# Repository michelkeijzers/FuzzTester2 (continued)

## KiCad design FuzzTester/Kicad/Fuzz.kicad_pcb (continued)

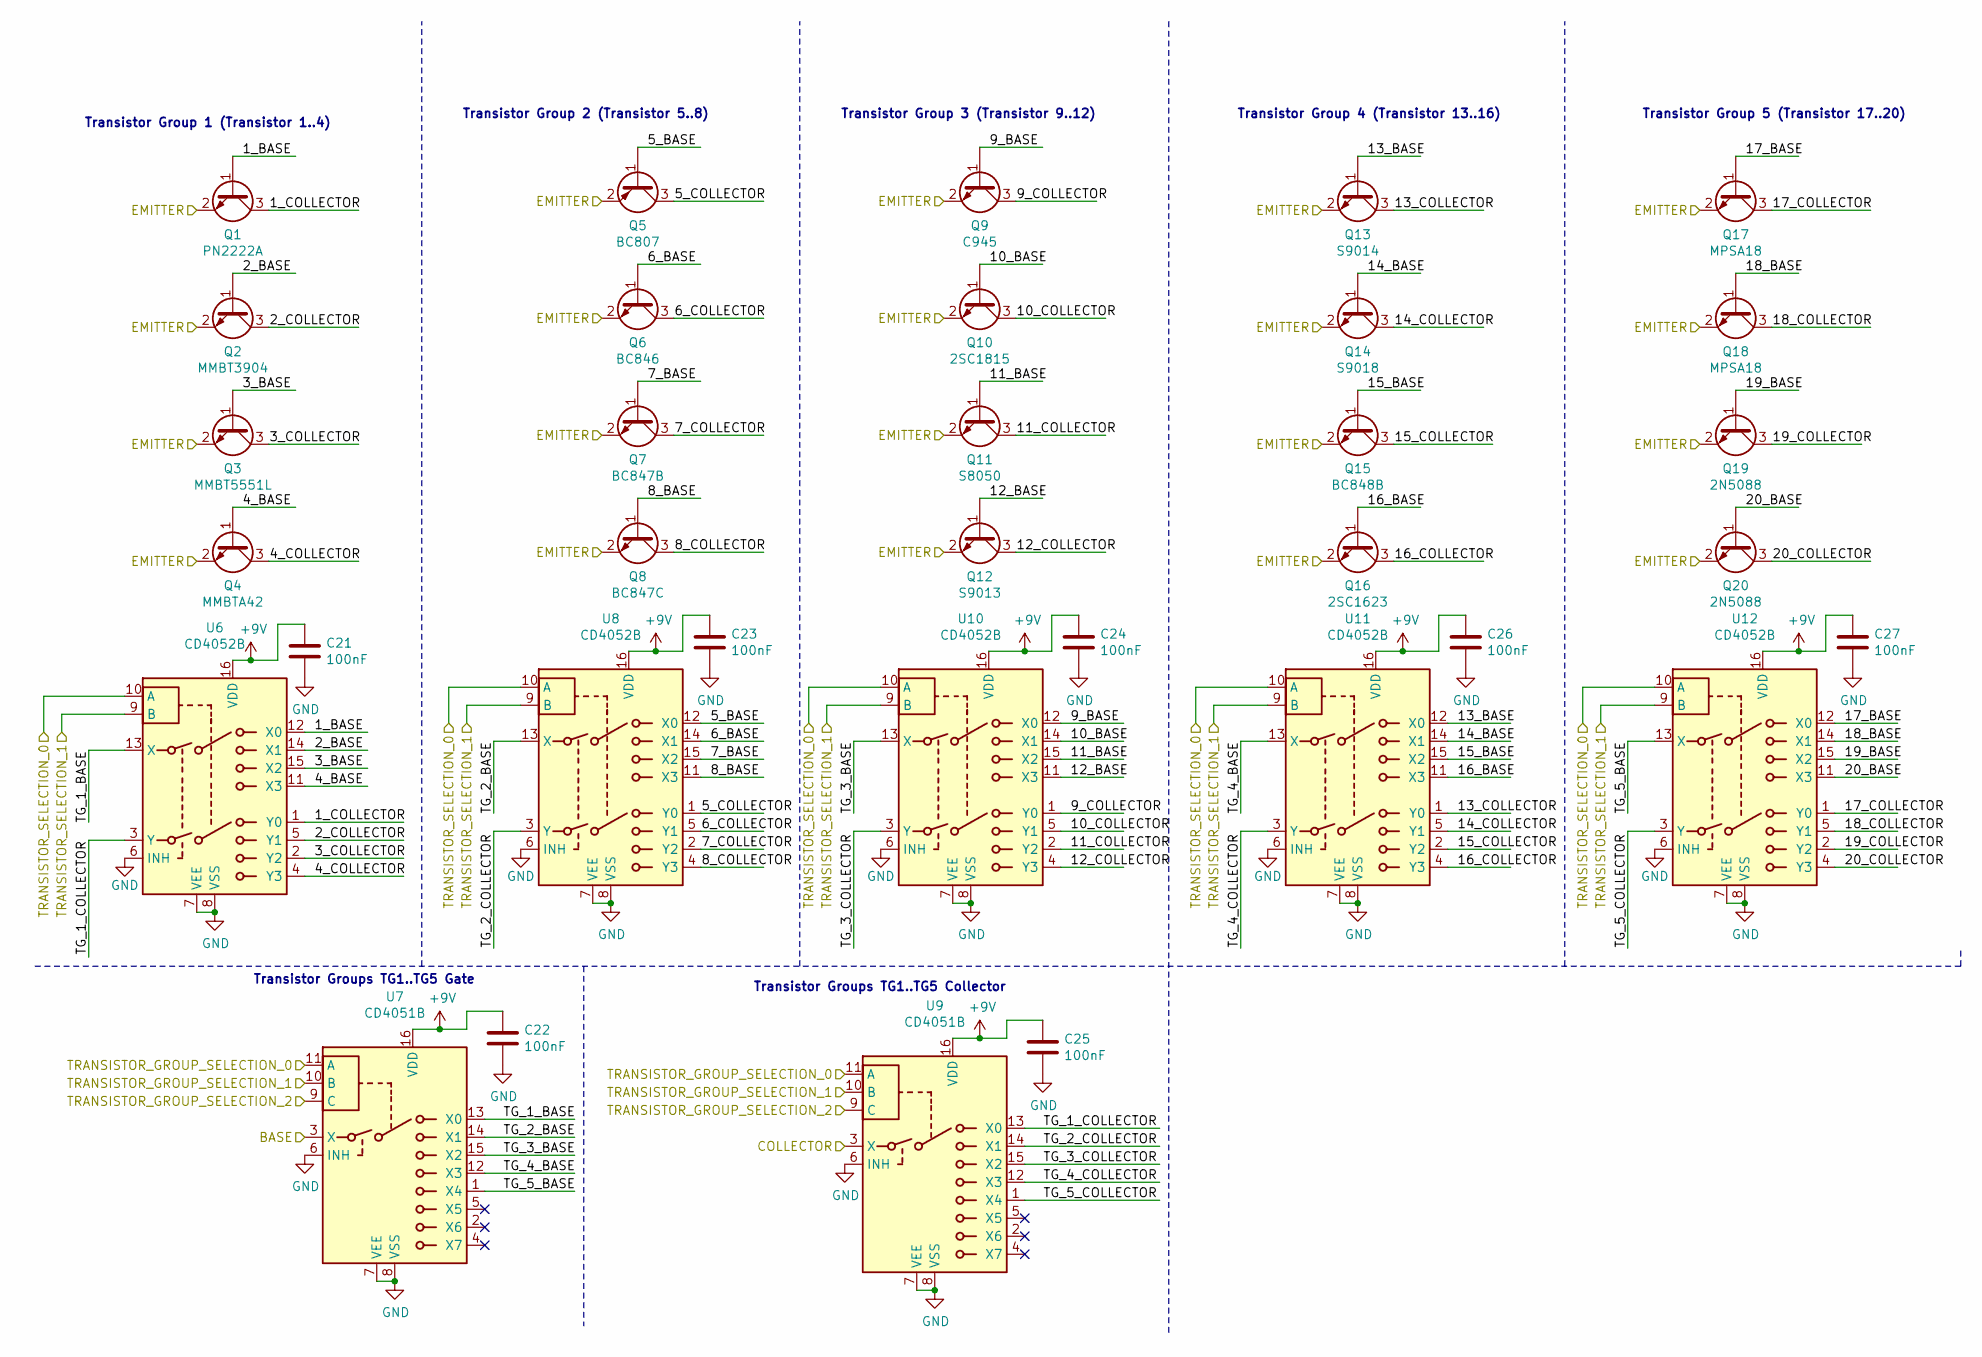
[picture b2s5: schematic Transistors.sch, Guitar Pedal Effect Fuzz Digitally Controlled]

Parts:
C21, C22, C23, C24, C25, C26, C27: 100nF; C_0805_2012Metric_Pad1.15x1.40mm_HandSolder
Q1: PN2222A; SOT-23_Handsoldering
Q2: MMBT3904; SOT-23_Handsoldering
Q3: MMBT5551L; SOT-23_Handsoldering
Q4: MMBTA42; SOT-23_Handsoldering
Q5: BC807; SOT-23_Handsoldering
Q6: BC846; SOT-23_Handsoldering
Q7: BC847B; SOT-23_Handsoldering
Q8: BC847C; SOT-23_Handsoldering
Q9: C945; SOT-23_Handsoldering
Q10: 2SC1815; SOT-23_Handsoldering
Q11: S8050; SOT-23_Handsoldering
Q12: S9013; SOT-23_Handsoldering
Q13: S9014; SOT-23_Handsoldering
Q14: S9018; SOT-23_Handsoldering
Q15: BC848B; SOT-23_Handsoldering
Q16: 2SC1623; SOT-23_Handsoldering
Q17, Q18: MPSA18; TO-92_Inline
Q19, Q20: 2N5088; TO-92_Inline
U6, U8, U10, U11, U12: CD4052B; SOIC-16_3.9x9.9mm_P1.27mm
U7, U9: CD4051B; SOIC-16_3.9x9.9mm_P1.27mm

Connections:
+9V: C21.1, C22.1, C23.1, C24.1, C25.1, C26.1, C27.1, U6.16 (VDD), U7.16 (VDD), U8.16 (VDD), U9.16 (VDD), U10.16 (VDD), U11.16 (VDD), U12.16 (VDD); also elsewhere on the board
/TRANSISTOR_B_GROUP_SELECTION_0: U7.11 (A), U9.11 (A); also elsewhere on the board
/TRANSISTOR_B_GROUP_SELECTION_1: U7.10 (B), U9.10 (B); also elsewhere on the board
/TRANSISTOR_B_GROUP_SELECTION_2: U7.9 (C), U9.9 (C); also elsewhere on the board
/TRANSISTOR_B_SELECTION_0: U6.10 (A), U8.10 (A), U10.10 (A), U11.10 (A), U12.10 (A); also elsewhere on the board
/TRANSISTOR_B_SELECTION_1: U6.9 (B), U8.9 (B), U10.9 (B), U11.9 (B), U12.9 (B); also elsewhere on the board
/TransistorsB/1_BASE: Q1.1 (B), U6.12 (X0)
/TransistorsB/1_COLLECTOR: Q1.3 (C), U6.1 (Y0)
/TransistorsB/2_BASE: Q2.1 (B), U6.14 (X1)
/TransistorsB/2_COLLECTOR: Q2.3 (C), U6.5 (Y1)
/TransistorsB/3_BASE: Q3.1 (B), U6.15 (X2)
/TransistorsB/3_COLLECTOR: Q3.3 (C), U6.2 (Y2)
/TransistorsB/4_BASE: Q4.1 (B), U6.11 (X3)
/TransistorsB/4_COLLECTOR: Q4.3 (C), U6.4 (Y3)
/TransistorsB/5_BASE: Q5.1 (B), U8.12 (X0)
/TransistorsB/5_COLLECTOR: Q5.3 (C), U8.1 (Y0)
/TransistorsB/6_BASE: Q6.1 (B), U8.14 (X1)
/TransistorsB/6_COLLECTOR: Q6.3 (C), U8.5 (Y1)
/TransistorsB/7_BASE: Q7.1 (B), U8.15 (X2)
/TransistorsB/7_COLLECTOR: Q7.3 (C), U8.2 (Y2)
/TransistorsB/8_BASE: Q8.1 (B), U8.11 (X3)
/TransistorsB/8_COLLECTOR: Q8.3 (C), U8.4 (Y3)
/TransistorsB/9_BASE: Q9.1 (B), U10.12 (X0)
/TransistorsB/9_COLLECTOR: Q9.3 (C), U10.1 (Y0)
/TransistorsB/10_BASE: Q10.1 (B), U10.14 (X1)
/TransistorsB/10_COLLECTOR: Q10.3 (C), U10.5 (Y1)
/TransistorsB/11_BASE: Q11.1 (B), U10.15 (X2)
/TransistorsB/11_COLLECTOR: Q11.3 (C), U10.2 (Y2)
/TransistorsB/12_BASE: Q12.1 (B), U10.11 (X3)
/TransistorsB/12_COLLECTOR: Q12.3 (C), U10.4 (Y3)
/TransistorsB/13_BASE: Q13.1 (B), U11.12 (X0)
/TransistorsB/13_COLLECTOR: Q13.3 (C), U11.1 (Y0)
/TransistorsB/14_BASE: Q14.1 (B), U11.14 (X1)
/TransistorsB/14_COLLECTOR: Q14.3 (C), U11.5 (Y1)
/TransistorsB/15_BASE: Q15.1 (B), U11.15 (X2)
/TransistorsB/15_COLLECTOR: Q15.3 (C), U11.2 (Y2)
/TransistorsB/16_BASE: Q16.1 (B), U11.11 (X3)
/TransistorsB/16_COLLECTOR: Q16.3 (C), U11.4 (Y3)
/TransistorsB/17_BASE: Q17.1 (B), U12.12 (X0)
/TransistorsB/17_COLLECTOR: Q17.3 (C), U12.1 (Y0)
/TransistorsB/18_BASE: Q18.1 (B), U12.14 (X1)
/TransistorsB/18_COLLECTOR: Q18.3 (C), U12.5 (Y1)
/TransistorsB/19_BASE: Q19.1 (B), U12.15 (X2)
/TransistorsB/19_COLLECTOR: Q19.3 (C), U12.2 (Y2)
/TransistorsB/20_BASE: Q20.1 (B), U12.11 (X3)
/TransistorsB/20_COLLECTOR: Q20.3 (C), U12.4 (Y3)
/TransistorsB/BASE: U7.3 (X); also elsewhere on the board
/TransistorsB/TG_1_BASE: U6.13 (X), U7.13 (X0)
/TransistorsB/TG_1_COLLECTOR: U6.3 (Y), U9.13 (X0)
/TransistorsB/TG_2_BASE: U7.14 (X1), U8.13 (X)
/TransistorsB/TG_2_COLLECTOR: U8.3 (Y), U9.14 (X1)
/TransistorsB/TG_3_BASE: U7.15 (X2), U10.13 (X)
/TransistorsB/TG_3_COLLECTOR: U9.15 (X2), U10.3 (Y)
/TransistorsB/TG_4_BASE: U7.12 (X3), U11.13 (X)
/TransistorsB/TG_4_COLLECTOR: U9.12 (X3), U11.3 (Y)
/TransistorsB/TG_5_BASE: U7.1 (X4), U12.13 (X)
/TransistorsB/TG_5_COLLECTOR: U9.1 (X4), U12.3 (Y)
/TransistorsC/BASE: U9.3 (X); also elsewhere on the board
GND: C21.2, C22.2, C23.2, C24.2, C25.2, C26.2, C27.2, U6.6 (INH), U6.7 (VEE), U6.8 (VSS), U7.6 (INH), U7.7 (VEE), U7.8 (VSS), U8.6 (INH), U8.7 (VEE), U8.8 (VSS), U9.6 (INH), U9.7 (VEE), U9.8 (VSS), U10.6 (INH), U10.7 (VEE), U10.8 (VSS), U11.6 (INH), U11.7 (VEE), U11.8 (VSS), U12.6 (INH), U12.7 (VEE), U12.8 (VSS); also elsewhere on the board
GNDA: Q1.2 (E), Q2.2 (E), Q3.2 (E), Q4.2 (E), Q5.2 (E), Q6.2 (E), Q7.2 (E), Q8.2 (E), Q9.2 (E), Q10.2 (E), Q11.2 (E), Q12.2 (E), Q13.2 (E), Q14.2 (E), Q15.2 (E), Q16.2 (E), Q17.2 (E), Q18.2 (E), Q19.2 (E), Q20.2 (E); also elsewhere on the board

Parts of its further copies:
C28, C29, C30, C31, C32, C33, C34: 100nF; C_0805_2012Metric_Pad1.15x1.40mm_HandSolder
Q21: PN2222A; SOT-23_Handsoldering
Q22: MMBT3904; SOT-23_Handsoldering
Q23: MMBT5551L; SOT-23_Handsoldering
Q24: MMBTA42; SOT-23_Handsoldering
Q25: BC807; SOT-23_Handsoldering
Q26: BC846; SOT-23_Handsoldering
Q27: BC847B; SOT-23_Handsoldering
Q28: BC847C; SOT-23_Handsoldering
Q29: C945; SOT-23_Handsoldering
Q30: 2SC1815; SOT-23_Handsoldering
Q31: S8050; SOT-23_Handsoldering
Q32: S9013; SOT-23_Handsoldering
Q33: S9014; SOT-23_Handsoldering
Q34: S9018; SOT-23_Handsoldering
Q35: BC848B; SOT-23_Handsoldering
Q36: 2SC1623; SOT-23_Handsoldering
Q37, Q38: MPSA18; TO-92_Inline
Q39, Q40: 2N5088; TO-92_Inline
U13, U15, U17, U18, U19: CD4052B; SOIC-16_3.9x9.9mm_P1.27mm
U14, U16: CD4051B; SOIC-16_3.9x9.9mm_P1.27mm

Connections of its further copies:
+9V: C28.1, C29.1, C30.1, C31.1, C32.1, C33.1, C34.1, U13.16 (VDD), U14.16 (VDD), U15.16 (VDD), U16.16 (VDD), U17.16 (VDD), U18.16 (VDD), U19.16 (VDD); also elsewhere on the board
/CapacitorsD/CAPACITOR_AUDIO_INPUT: U16.3 (X); also elsewhere on the board
/TRANSISTOR_C_GROUP_SELECTION_0: U14.11 (A), U16.11 (A); also elsewhere on the board
/TRANSISTOR_C_GROUP_SELECTION_1: U14.10 (B), U16.10 (B); also elsewhere on the board
/TRANSISTOR_C_GROUP_SELECTION_2: U14.9 (C), U16.9 (C); also elsewhere on the board
/TRANSISTOR_C_SELECTION_0: U13.10 (A), U15.10 (A), U17.10 (A), U18.10 (A), U19.10 (A); also elsewhere on the board
/TRANSISTOR_C_SELECTION_1: U13.9 (B), U15.9 (B), U17.9 (B), U18.9 (B), U19.9 (B); also elsewhere on the board
/TransistorsC/1_BASE: Q21.1 (B), U13.12 (X0)
/TransistorsC/1_COLLECTOR: Q21.3 (C), U13.1 (Y0)
/TransistorsC/2_BASE: Q22.1 (B), U13.14 (X1)
/TransistorsC/2_COLLECTOR: Q22.3 (C), U13.5 (Y1)
/TransistorsC/3_BASE: Q23.1 (B), U13.15 (X2)
/TransistorsC/3_COLLECTOR: Q23.3 (C), U13.2 (Y2)
/TransistorsC/4_BASE: Q24.1 (B), U13.11 (X3)
/TransistorsC/4_COLLECTOR: Q24.3 (C), U13.4 (Y3)
/TransistorsC/5_BASE: Q25.1 (B), U15.12 (X0)
/TransistorsC/5_COLLECTOR: Q25.3 (C), U15.1 (Y0)
/TransistorsC/6_BASE: Q26.1 (B), U15.14 (X1)
/TransistorsC/6_COLLECTOR: Q26.3 (C), U15.5 (Y1)
/TransistorsC/7_BASE: Q27.1 (B), U15.15 (X2)
/TransistorsC/7_COLLECTOR: Q27.3 (C), U15.2 (Y2)
/TransistorsC/8_BASE: Q28.1 (B), U15.11 (X3)
/TransistorsC/8_COLLECTOR: Q28.3 (C), U15.4 (Y3)
/TransistorsC/9_BASE: Q29.1 (B), U17.12 (X0)
/TransistorsC/9_COLLECTOR: Q29.3 (C), U17.1 (Y0)
/TransistorsC/10_BASE: Q30.1 (B), U17.14 (X1)
/TransistorsC/10_COLLECTOR: Q30.3 (C), U17.5 (Y1)
/TransistorsC/11_BASE: Q31.1 (B), U17.15 (X2)
/TransistorsC/11_COLLECTOR: Q31.3 (C), U17.2 (Y2)
/TransistorsC/12_BASE: Q32.1 (B), U17.11 (X3)
/TransistorsC/12_COLLECTOR: Q32.3 (C), U17.4 (Y3)
/TransistorsC/13_BASE: Q33.1 (B), U18.12 (X0)
/TransistorsC/13_COLLECTOR: Q33.3 (C), U18.1 (Y0)
/TransistorsC/14_BASE: Q34.1 (B), U18.14 (X1)
/TransistorsC/14_COLLECTOR: Q34.3 (C), U18.5 (Y1)
/TransistorsC/15_BASE: Q35.1 (B), U18.15 (X2)
/TransistorsC/15_COLLECTOR: Q35.3 (C), U18.2 (Y2)
/TransistorsC/16_BASE: Q36.1 (B), U18.11 (X3)
/TransistorsC/16_COLLECTOR: Q36.3 (C), U18.4 (Y3)
/TransistorsC/17_BASE: Q37.1 (B), U19.12 (X0)
/TransistorsC/17_COLLECTOR: Q37.3 (C), U19.1 (Y0)
/TransistorsC/18_BASE: Q38.1 (B), U19.14 (X1)
/TransistorsC/18_COLLECTOR: Q38.3 (C), U19.5 (Y1)
/TransistorsC/19_BASE: Q39.1 (B), U19.15 (X2)
/TransistorsC/19_COLLECTOR: Q39.3 (C), U19.2 (Y2)
/TransistorsC/20_BASE: Q40.1 (B), U19.11 (X3)
/TransistorsC/20_COLLECTOR: Q40.3 (C), U19.4 (Y3)
/TransistorsC/BASE: U14.3 (X); also elsewhere on the board
/TransistorsC/EMITTER: Q21.2 (E), Q22.2 (E), Q23.2 (E), Q24.2 (E), Q25.2 (E), Q26.2 (E), Q27.2 (E), Q28.2 (E), Q29.2 (E), Q30.2 (E), Q31.2 (E), Q32.2 (E), Q33.2 (E), Q34.2 (E), Q35.2 (E), Q36.2 (E), Q37.2 (E), Q38.2 (E), Q39.2 (E), Q40.2 (E); also elsewhere on the board
/TransistorsC/TG_1_BASE: U13.13 (X), U14.13 (X0)
/TransistorsC/TG_1_COLLECTOR: U13.3 (Y), U16.13 (X0)
/TransistorsC/TG_2_BASE: U14.14 (X1), U15.13 (X)
/TransistorsC/TG_2_COLLECTOR: U15.3 (Y), U16.14 (X1)
/TransistorsC/TG_3_BASE: U14.15 (X2), U17.13 (X)
/TransistorsC/TG_3_COLLECTOR: U16.15 (X2), U17.3 (Y)
/TransistorsC/TG_4_BASE: U14.12 (X3), U18.13 (X)
/TransistorsC/TG_4_COLLECTOR: U16.12 (X3), U18.3 (Y)
/TransistorsC/TG_5_BASE: U14.1 (X4), U19.13 (X)
/TransistorsC/TG_5_COLLECTOR: U16.1 (X4), U19.3 (Y)
GND: C28.2, C29.2, C30.2, C31.2, C32.2, C33.2, C34.2, U13.6 (INH), U13.7 (VEE), U13.8 (VSS), U14.6 (INH), U14.7 (VEE), U14.8 (VSS), U15.6 (INH), U15.7 (VEE), U15.8 (VSS), U16.6 (INH), U16.7 (VEE), U16.8 (VSS), U17.6 (INH), U17.7 (VEE), U17.8 (VSS), U18.6 (INH), U18.7 (VEE), U18.8 (VSS), U19.6 (INH), U19.7 (VEE), U19.8 (VSS); also elsewhere on the board

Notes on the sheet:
Transistor Group 4 (Transistor 13..16)
Transistor Group 5 (Transistor 17..20)
Transistor Group 2 (Transistor 5..8)
Transistor Group 1 (Transistor 1..4)
Transistor Groups TG1..TG5 Collector
Transistor Group 3 (Transistor 9..12)
Transistor Groups TG1..TG5 Gate

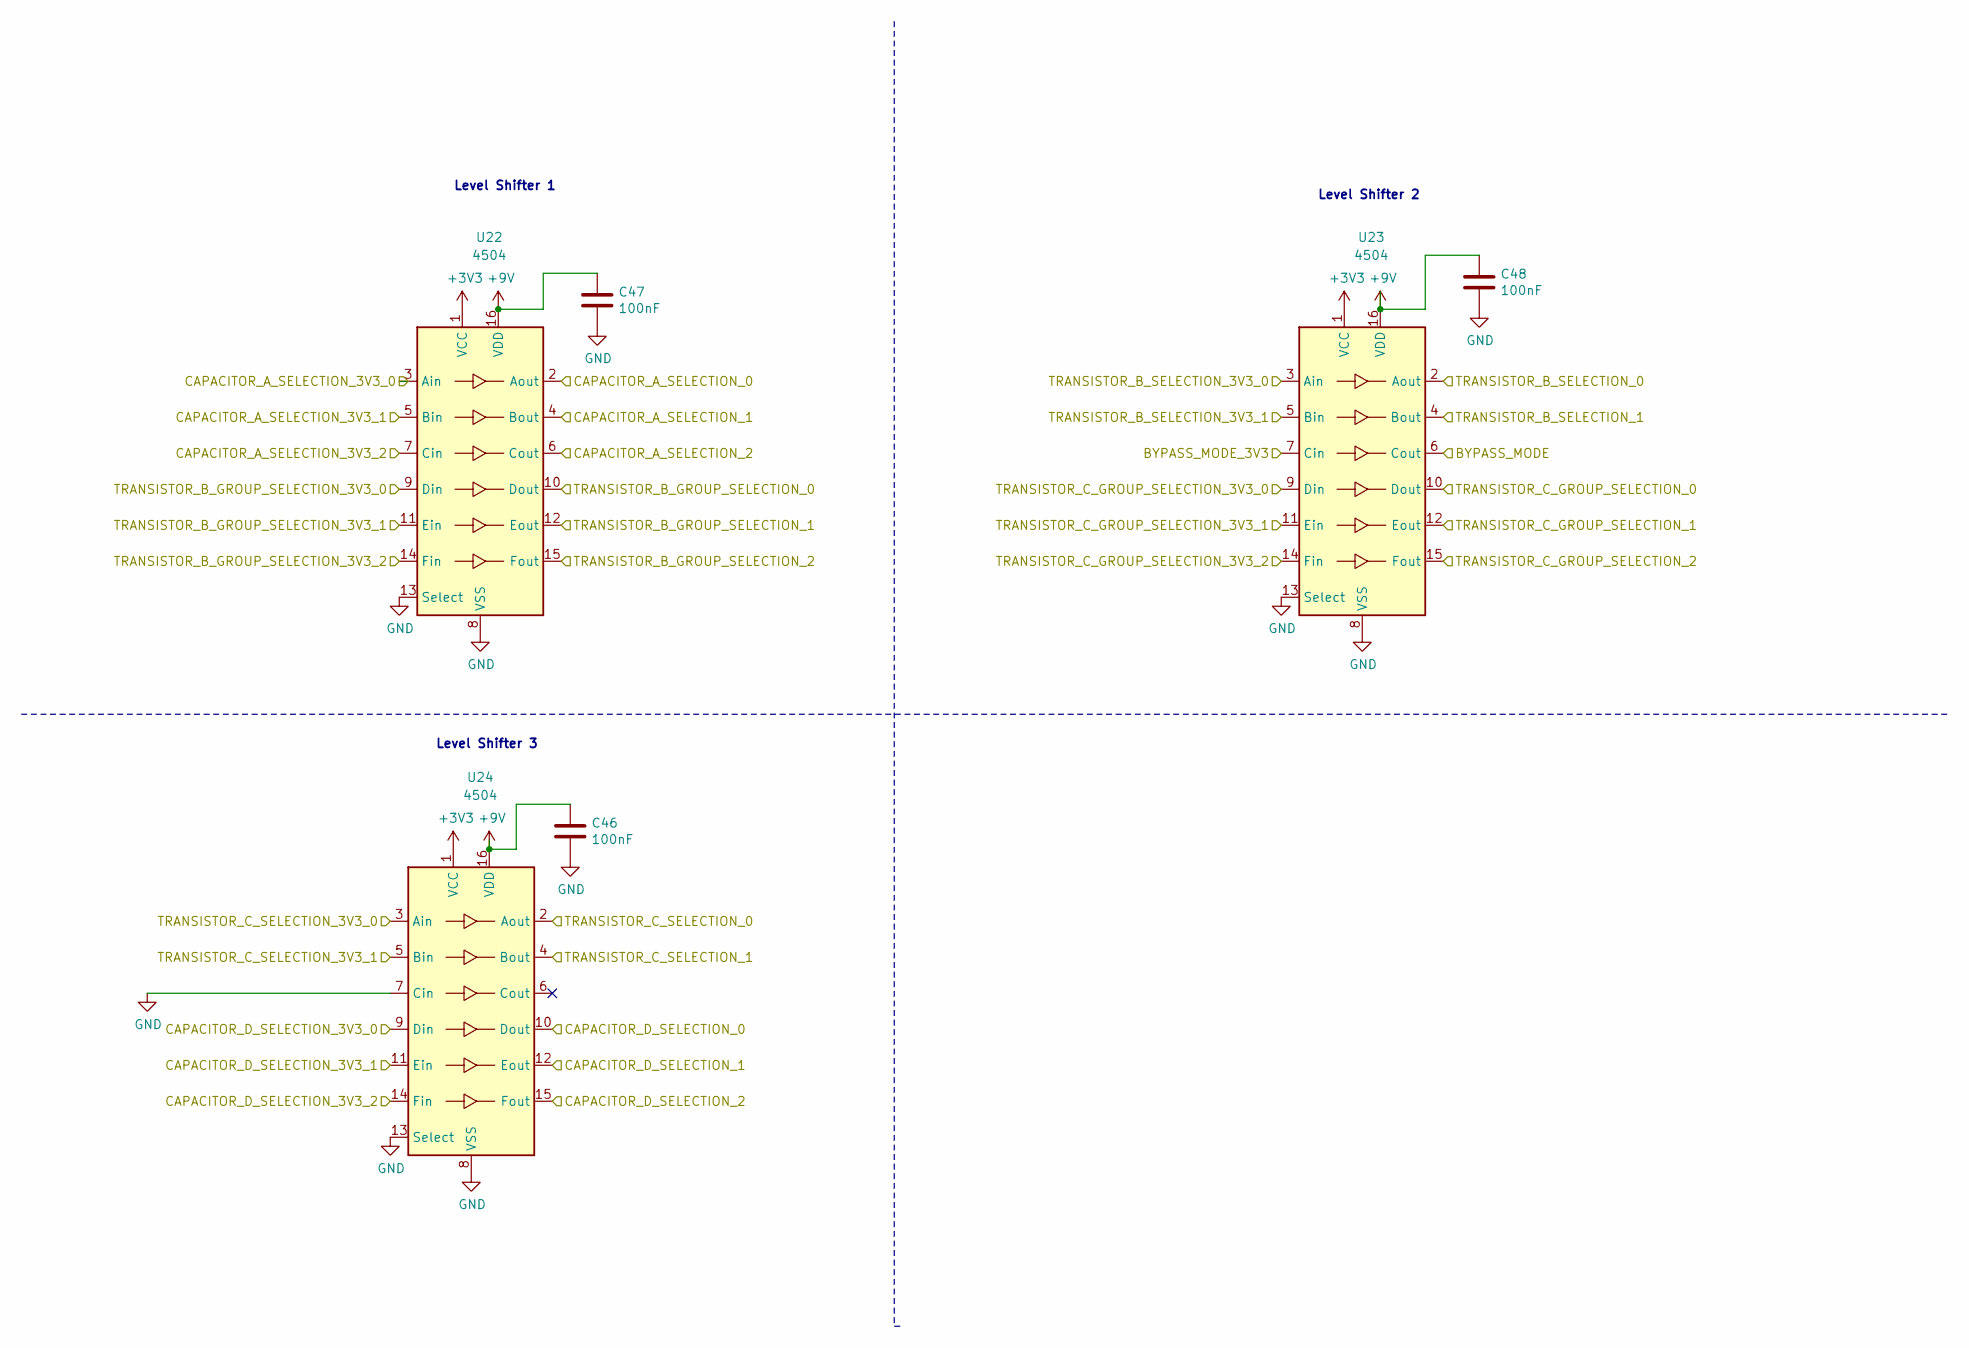
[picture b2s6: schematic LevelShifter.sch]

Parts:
C46, C47, C48: 100nF; C_0805_2012Metric_Pad1.15x1.40mm_HandSolder
U22, U23, U24: 4504; SOIC-16_3.9x9.9mm_P1.27mm

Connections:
+3V3: U22.1 (VCC), U23.1 (VCC), U24.1 (VCC); also elsewhere on the board
+9V: C46.1, C47.1, C48.1, U22.16 (VDD), U23.16 (VDD), U24.16 (VDD); also elsewhere on the board
/BYPASS_MODE: U23.6 (Cout); also elsewhere on the board
/BYPASS_MODE_3V3: U23.7 (Cin); also elsewhere on the board
/CAPACITOR_A_SELECTION_0: U22.2 (Aout); also elsewhere on the board
/CAPACITOR_A_SELECTION_1: U22.4 (Bout); also elsewhere on the board
/CAPACITOR_A_SELECTION_2: U22.6 (Cout); also elsewhere on the board
/CAPACITOR_A_SELECTION_3V3_0: U22.3 (Ain); also elsewhere on the board
/CAPACITOR_A_SELECTION_3V3_1: U22.5 (Bin); also elsewhere on the board
/CAPACITOR_A_SELECTION_3V3_2: U22.7 (Cin); also elsewhere on the board
/CAPACITOR_D_SELECTION_0: U24.10 (Dout); also elsewhere on the board
/CAPACITOR_D_SELECTION_1: U24.12 (Eout); also elsewhere on the board
/CAPACITOR_D_SELECTION_2: U24.15 (Fout); also elsewhere on the board
/CAPACITOR_D_SELECTION_3V3_0: U24.9 (Din); also elsewhere on the board
/CAPACITOR_D_SELECTION_3V3_1: U24.11 (Ein); also elsewhere on the board
/CAPACITOR_D_SELECTION_3V3_2: U24.14 (Fin); also elsewhere on the board
/TRANSISTOR_B_GROUP_SELECTION_0: U22.10 (Dout); also elsewhere on the board
/TRANSISTOR_B_GROUP_SELECTION_1: U22.12 (Eout); also elsewhere on the board
/TRANSISTOR_B_GROUP_SELECTION_2: U22.15 (Fout); also elsewhere on the board
/TRANSISTOR_B_GROUP_SELECTION_3V3_0: U22.9 (Din); also elsewhere on the board
/TRANSISTOR_B_GROUP_SELECTION_3V3_1: U22.11 (Ein); also elsewhere on the board
/TRANSISTOR_B_GROUP_SELECTION_3V3_2: U22.14 (Fin); also elsewhere on the board
/TRANSISTOR_B_SELECTION_0: U23.2 (Aout); also elsewhere on the board
/TRANSISTOR_B_SELECTION_1: U23.4 (Bout); also elsewhere on the board
/TRANSISTOR_B_SELECTION_3V3_0: U23.3 (Ain); also elsewhere on the board
/TRANSISTOR_B_SELECTION_3V3_1: U23.5 (Bin); also elsewhere on the board
/TRANSISTOR_C_GROUP_SELECTION_0: U23.10 (Dout); also elsewhere on the board
/TRANSISTOR_C_GROUP_SELECTION_1: U23.12 (Eout); also elsewhere on the board
/TRANSISTOR_C_GROUP_SELECTION_2: U23.15 (Fout); also elsewhere on the board
/TRANSISTOR_C_GROUP_SELECTION_3V3_0: U23.9 (Din); also elsewhere on the board
/TRANSISTOR_C_GROUP_SELECTION_3V3_1: U23.11 (Ein); also elsewhere on the board
/TRANSISTOR_C_GROUP_SELECTION_3V3_2: U23.14 (Fin); also elsewhere on the board
/TRANSISTOR_C_SELECTION_0: U24.2 (Aout); also elsewhere on the board
/TRANSISTOR_C_SELECTION_1: U24.4 (Bout); also elsewhere on the board
/TRANSISTOR_C_SELECTION_3V3_0: U24.3 (Ain); also elsewhere on the board
/TRANSISTOR_C_SELECTION_3V3_1: U24.5 (Bin); also elsewhere on the board
GND: C46.2, C47.2, C48.2, U22.8 (VSS), U22.13 (Select), U23.8 (VSS), U23.13 (Select), U24.7 (Cin), U24.8 (VSS), U24.13 (Select); also elsewhere on the board

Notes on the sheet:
Level Shifter 1
Level Shifter 2
Level Shifter 3

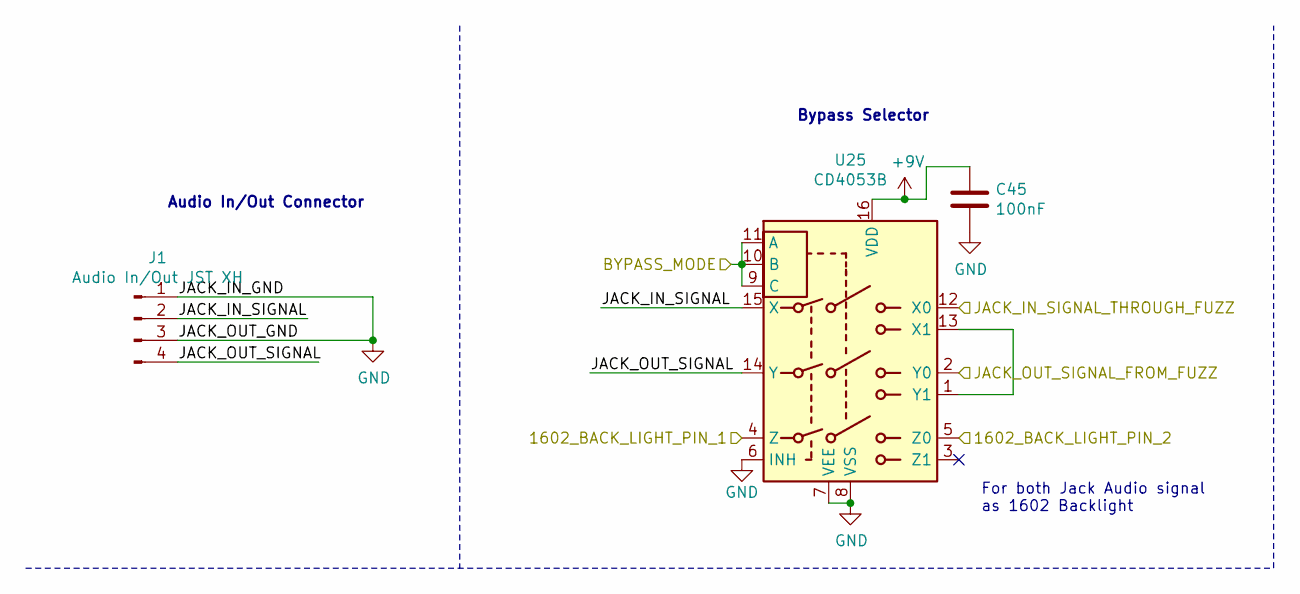
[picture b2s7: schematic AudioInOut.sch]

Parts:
C45: 100nF; C_0805_2012Metric_Pad1.15x1.40mm_HandSolder
J1: Audio In/Out JST XH; JST_XH_B4B-XH-A_1x04_P2.50mm_Vertical
U25: CD4053B; SOIC-16_3.9x9.9mm_P1.27mm

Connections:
+9V: C45.1, U25.16 (VDD); also elsewhere on the board
/1602_BACK_LIGHT_PIN_1: U25.4 (Z); also elsewhere on the board
/1602_BACK_LIGHT_PIN_2: U25.5 (Z0); also elsewhere on the board
/AudioInOut/JACK_IN_SIGNAL: J1.2, U25.15 (X)
/AudioInOut/JACK_OUT_SIGNAL: J1.4, U25.14 (Y)
/BYPASS_MODE: U25.9 (C), U25.10 (B), U25.11 (A); also elsewhere on the board
/JACK_IN_SIGNAL_THROUGH_FUZZ: U25.12 (X0); also elsewhere on the board
/JACK_OUT_SIGNAL_FROM_FUZZ: U25.2 (Y0); also elsewhere on the board
GND: C45.2, J1.1, J1.3, U25.6 (INH), U25.7 (VEE), U25.8 (VSS); also elsewhere on the board
unnamed: U25.1 (Y1), U25.13 (X1)

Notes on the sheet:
Bypass Selector
Audio In/Out Connector
For both Jack Audio signal as 1602 Backlight

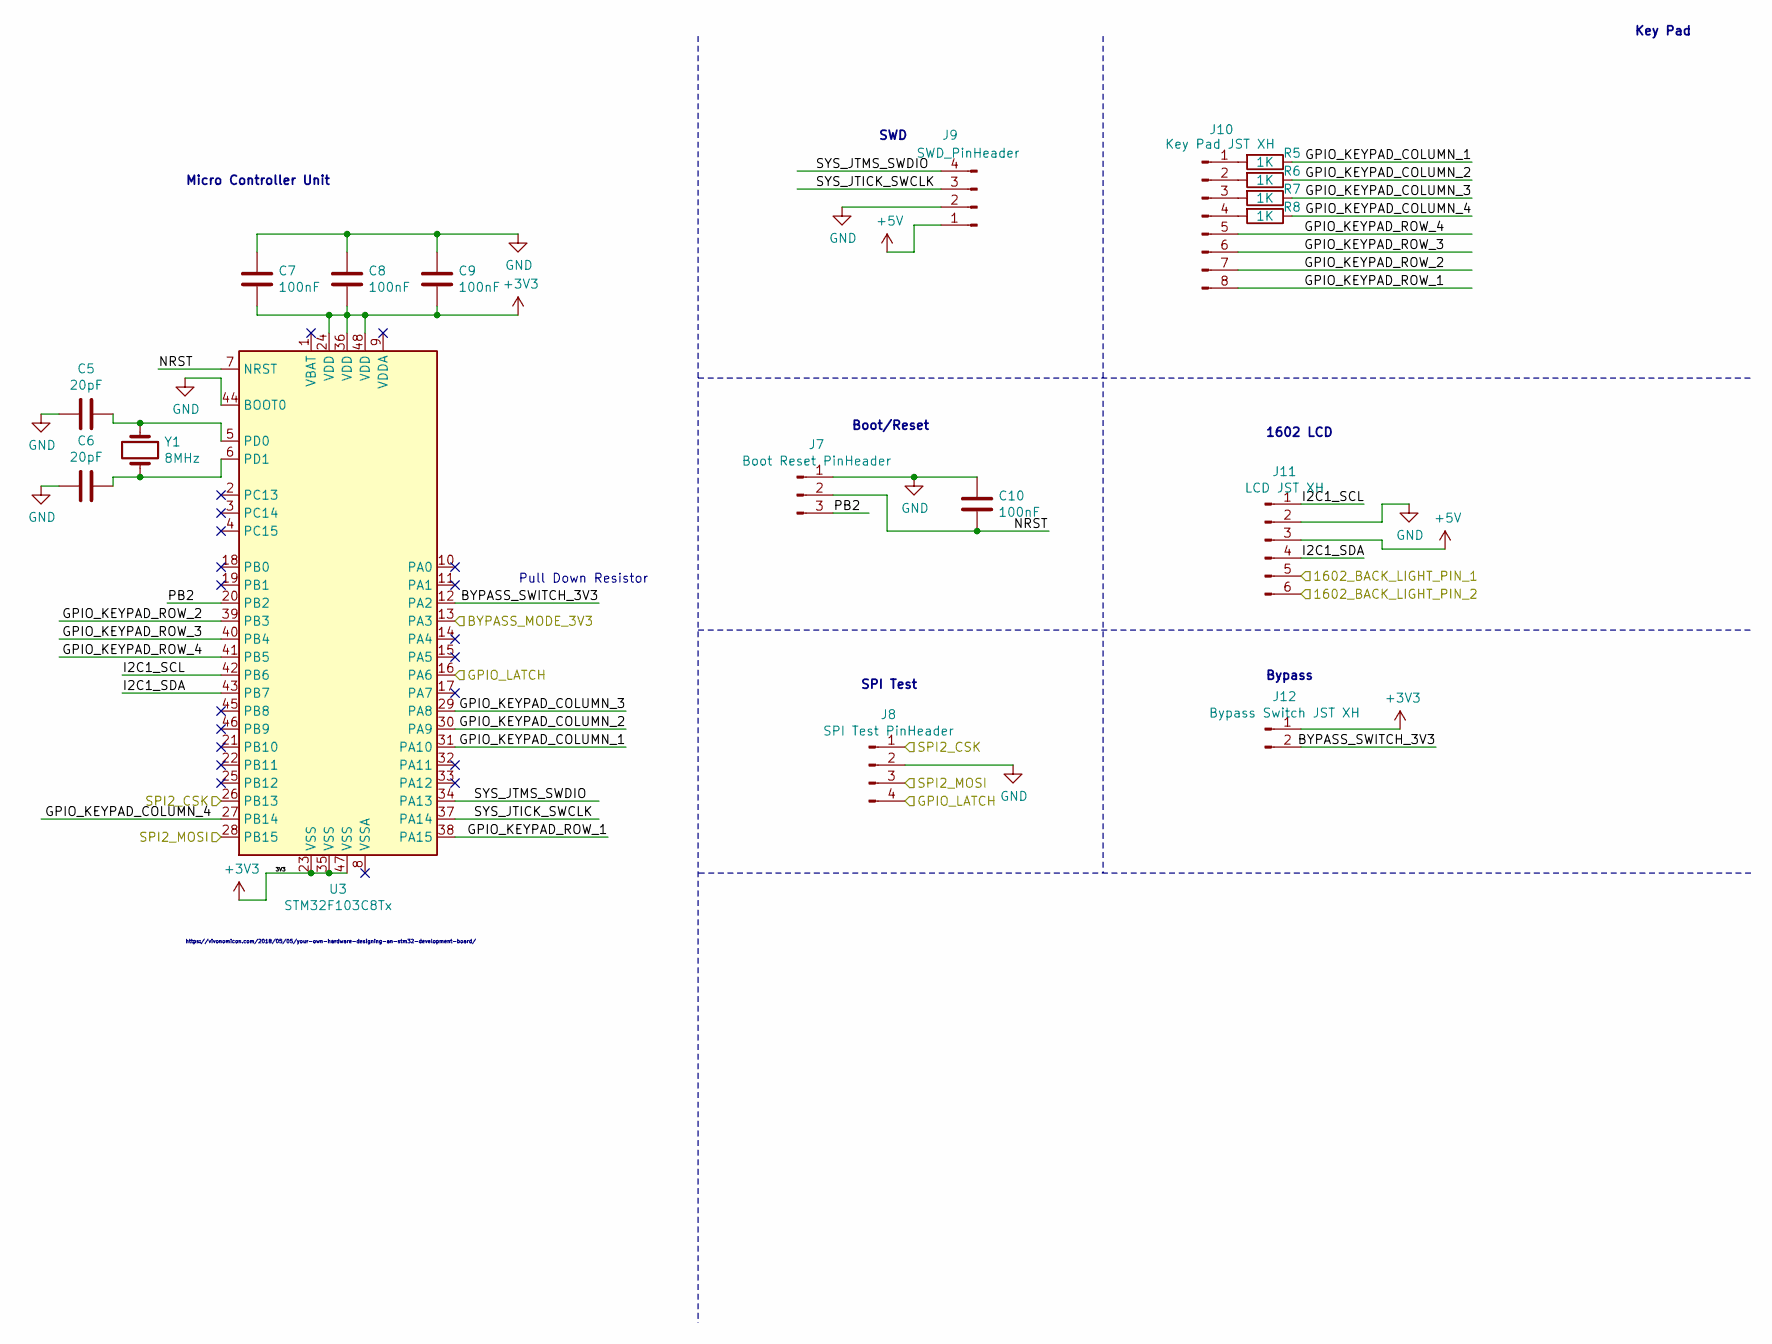
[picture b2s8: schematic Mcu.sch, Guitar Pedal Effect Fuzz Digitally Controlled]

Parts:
C5, C6: 20pF; C_0805_2012Metric_Pad1.15x1.40mm_HandSolder
C7, C8, C9, C10: 100nF; C_0805_2012Metric_Pad1.15x1.40mm_HandSolder
J7: Boot Reset PinHeader; PinHeader_1x03_P2.54mm_Vertical
J8: SPI Test PinHeader; PinHeader_1x04_P2.54mm_Vertical
J9: SWD_PinHeader; PinHeader_1x04_P2.54mm_Vertical
J10: Key Pad JST XH; JST_XH_B8B-XH-A_1x08_P2.50mm_Vertical
J11: LCD JST XH; JST_XH_B6B-XH-A_1x06_P2.50mm_Vertical
J12: Bypass Switch JST XH; JST_XH_B2B-XH-A_1x02_P2.50mm_Vertical
R5, R6, R7, R8: 1K; R_0805_2012Metric_Pad1.15x1.40mm_HandSolder
U3: STM32F103C8Tx; LQFP-48_7x7mm_P0.5mm
Y1: 8MHz; Crystal_HC49-U_Vertical

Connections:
+3V3: C7.2, C8.2, C9.2, J12.1, U3.23 (VSS), U3.24 (VDD), U3.35 (VSS), U3.36 (VDD), U3.47 (VSS), U3.48 (VDD); also elsewhere on the board
+5V: J9.1, J11.3; also elsewhere on the board
/1602_BACK_LIGHT_PIN_1: J11.5; also elsewhere on the board
/1602_BACK_LIGHT_PIN_2: J11.6; also elsewhere on the board
/BYPASS_MODE_3V3: U3.13 (PA3); also elsewhere on the board
/Mcu/BYPASS_SWITCH_3V3: J12.2, U3.12 (PA2)
/Mcu/GPIO_KEYPAD_COLUMN_1: R5.1, U3.31 (PA10)
/Mcu/GPIO_KEYPAD_COLUMN_2: R6.1, U3.30 (PA9)
/Mcu/GPIO_KEYPAD_COLUMN_3: R7.1, U3.29 (PA8)
/Mcu/GPIO_KEYPAD_COLUMN_4: R8.1, U3.27 (PB14)
/Mcu/GPIO_KEYPAD_ROW_1: J10.8, U3.38 (PA15)
/Mcu/GPIO_KEYPAD_ROW_2: J10.7, U3.39 (PB3)
/Mcu/GPIO_KEYPAD_ROW_3: J10.6, U3.40 (PB4)
/Mcu/GPIO_KEYPAD_ROW_4: J10.5, U3.41 (PB5)
/Mcu/NRST: C10.1, J7.2, U3.7 (NRST)
/Mcu/PB2: J7.3, U3.20 (PB2)
GND: C5.2, C6.2, C7.1, C8.1, C9.1, C10.2, J7.1, J8.2, J9.2, J11.2, U3.44 (BOOT0); also elsewhere on the board
unnamed: C5.1, U3.5 (PD0), Y1.1
unnamed: C6.1, U3.6 (PD1), Y1.2
unnamed: J10.1, R5.2
unnamed: J10.2, R6.2
unnamed: J10.3, R7.2
unnamed: J10.4, R8.2

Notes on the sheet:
Micro Controller Unit
https://vivonomicon.com/2018/05/05/your-own-hardware-designing-an-stm32-development-board/
Boot/Reset
SPI Test
SWD
Key Pad
1602 LCD
Bypass
Pull Down Resistor

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
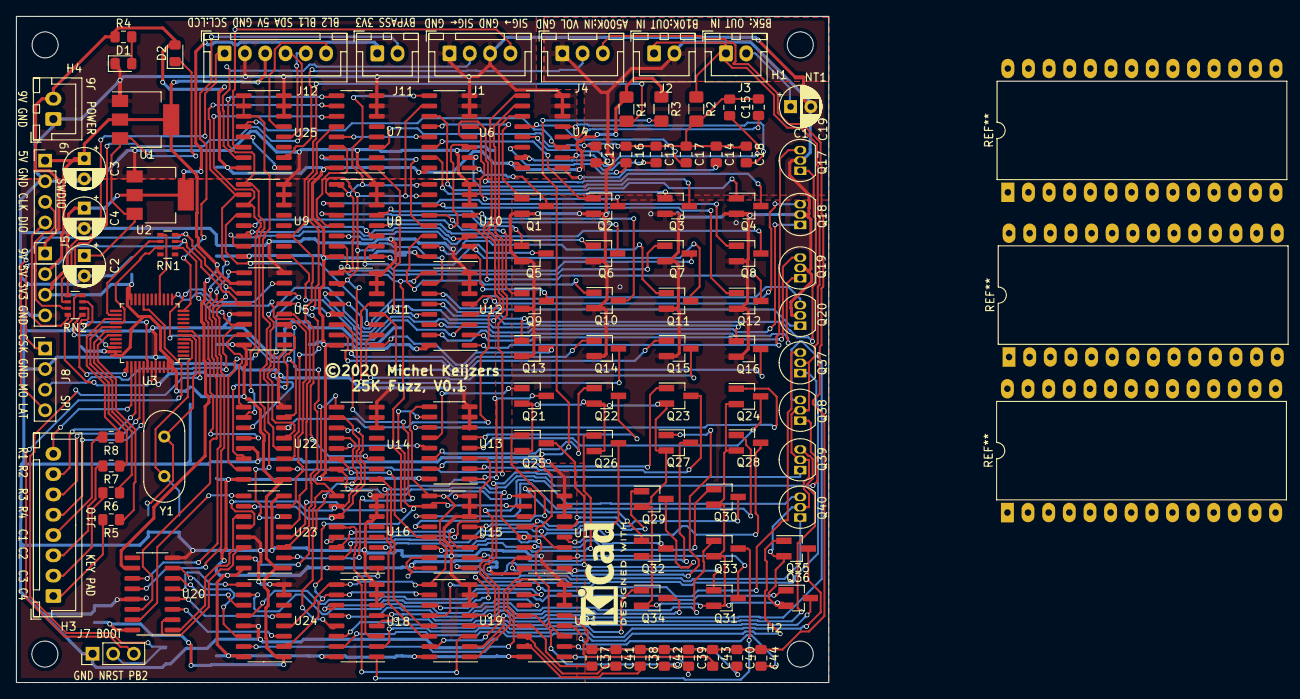
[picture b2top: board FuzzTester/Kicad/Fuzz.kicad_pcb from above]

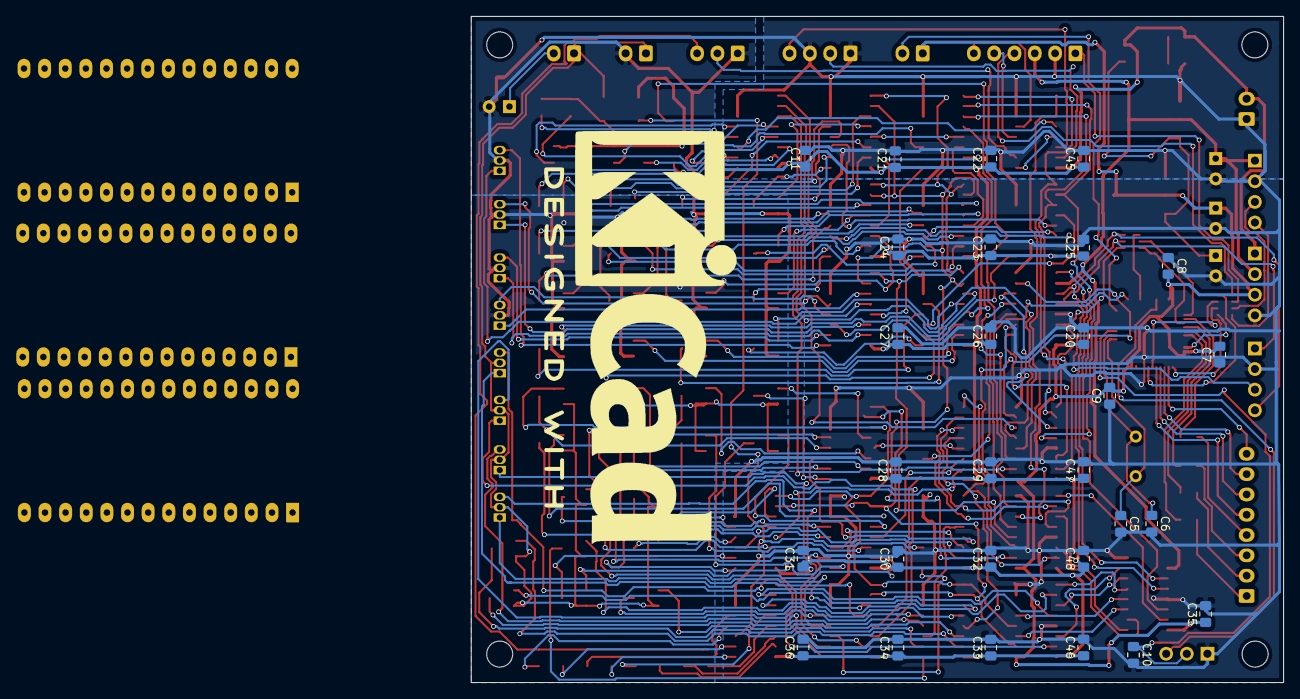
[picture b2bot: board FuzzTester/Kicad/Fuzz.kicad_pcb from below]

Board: 2 copper layers, 100.0 x 82.0 mm, 143 parts (28 on the bottom side), 202 nets.

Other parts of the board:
RN1, RN2: R_Pack04; R_Array_Convex_4x0603

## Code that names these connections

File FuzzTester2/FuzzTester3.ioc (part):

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Mcu.Name=STM32F103C(8-B)Tx
Mcu.Package=LQFP48
Mcu.UserName=STM32F103C8Tx
PA1.GPIOParameters=GPIO_Label
PA1.GPIO_Label=GPIO_TRANSISTOR_C_SELECTION_1
PA1.Signal=GPIO_Output
PA10.Mode=Asynchronous
PA10.Signal=USART1_RX
PA13.Mode=Serial_Wire
PA13.Signal=SYS_JTMS-SWDIO
PA14.Mode=Serial_Wire
PA14.Signal=SYS_JTCK-SWCLK
PA2.GPIOParameters=GPIO_PuPd,GPIO_Label
PA2.GPIO_Label=GPIO_BYPASS_SWITCH
PA2.GPIO_PuPd=GPIO_PULLDOWN
PA2.Signal=GPXTI2
PA3.GPIOParameters=GPIO_Label
PA3.GPIO_Label=GPIO_BYPASS_MODE
PA3.Signal=GPIO_Input
PA4.GPIOParameters=GPIO_Label
PA4.GPIO_Label=GPIO_TRANSISTOR_C_SELECTION_2
PA4.Signal=GPIO_Output
PA5.GPIOParameters=GPIO_Label
PA5.GPIO_Label=GPIO_TRANSISTOR_C_SELECTION_3
PA5.Signal=GPIO_Output
PA7.GPIOParameters=GPIO_Label
PA7.GPIO_Label=GPIO_CAPACITOR_D_SELECTION_0
PA7.Signal=GPIO_Output
PA8.GPIOParameters=GPIO_Label
PA8.GPIO_Label=GPIO_TRANSISTOR_C_SELECTION_0
PA8.Signal=GPIO_Input
PA9.Mode=Asynchronous
PA9.Signal=USART1_TX
PB0.GPIOParameters=GPIO_Label
PB0.GPIO_Label=GPIO_TRANSISTOR_B_SELECTION_0
PB0.Signal=GPIO_Output
PB1.GPIOParameters=GPIO_Label
PB1.GPIO_Label=GPIO_TRANSISTOR_B_SELECTION_1
PB1.Signal=GPIO_Output
PB10.GPIOParameters=GPIO_Label
PB10.GPIO_Label=GPIO_CAPACITOR_A_SELECTION_0
PB10.Signal=GPIO_Output
PB11.GPIOParameters=GPIO_Label
PB11.GPIO_Label=GPIO_CAPACITOR_A_SELECTION_1
PB11.Signal=GPIO_Output
PB12.GPIOParameters=GPIO_Label
PB12.GPIO_Label=GPIO_CAPACITOR_A_SELECTION_2
PB12.Signal=GPIO_Output
PB14.GPIOParameters=GPIO_Label
PB14.GPIO_Label=GPIO_CAPACITOR_D_SELECTION_1
PB14.Signal=GPIO_Output
PB15.GPIOParameters=GPIO_Label
PB15.GPIO_Label=GPIO_CAPACITOR_D_SELECTION_2
PB15.Signal=GPIO_Output
PB2.GPIOParameters=GPIO_PuPd,GPIO_Label
PB2.GPIO_Label=GPIO_PB2
PB2.GPIO_PuPd=GPIO_NOPULL
PB2.Signal=GPIO_Output
PB3.GPIOParameters=GPIO_PuPd,GPIO_Label
PB3.GPIO_Label=GPIO_BUTTON_DECREASE
PB3.GPIO_PuPd=GPIO_PULLDOWN
PB3.Signal=GPXTI3
PB4.GPIOParameters=GPIO_PuPd,GPIO_Label
PB4.GPIO_Label=GPIO_BUTTON_ENTER
PB4.GPIO_PuPd=GPIO_PULLDOWN
PB4.Signal=GPXTI4
PB5.GPIOParameters=GPIO_PuPd,GPIO_Label
PB5.GPIO_Label=GPIO_BUTTON_INCREASE
PB5.GPIO_PuPd=GPIO_PULLDOWN
PB5.Signal=GPXTI5
PB6.Mode=I2C
PB6.Signal=I2C1_SCL
PB7.Mode=I2C
PB7.Signal=I2C1_SDA
PB8.GPIOParameters=GPIO_Label
PB8.GPIO_Label=GPIO_TRANSISTOR_B_SELECTION_2
PB8.Signal=GPIO_Output
PB9.GPIOParameters=GPIO_Label
PB9.GPIO_Label=GPIO_TRANSISTOR_B_SELECTION_3
PB9.Signal=GPIO_Output
PD0-OSC_IN.Mode=HSE-External-Oscillator
PD0-OSC_IN.Signal=RCC_OSC_IN
PD1-OSC_OUT.Mode=HSE-External-Oscillator
PD1-OSC_OUT.Signal=RCC_OSC_OUT
RCC.SYSCLKFreq_VALUE=48000000
RCC.SYSCLKSource=RCC_SYSCLKSOURCE_PLLCLK
board=custom

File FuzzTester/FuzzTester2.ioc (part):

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Mcu.Name=STM32F103C(8-B)Tx
Mcu.Package=LQFP48
Mcu.UserName=STM32F103C8Tx
PA10.GPIOParameters=GPIO_Label
PA10.GPIO_Label=GPIO_KEYPAD_COLUMN_1
PA10.Signal=GPIO_Input
PA13.Mode=Serial_Wire
PA13.Signal=SYS_JTMS-SWDIO
PA14.Mode=Serial_Wire
PA14.Signal=SYS_JTCK-SWCLK
PA15.GPIOParameters=GPIO_Speed,GPIO_Label
PA15.GPIO_Label=GPIO_KEYPAD_ROW_4
PA15.GPIO_Speed=GPIO_SPEED_FREQ_HIGH
PA15.Signal=GPIO_Output
PA5.Mode=TX_Only_Simplex_Unidirect_Master
PA5.Signal=SPI1_SCK
PA6.GPIOParameters=GPIO_Label
PA6.GPIO_Label=GPIO_LATCH
PA6.Signal=GPIO_Output
PA7.Mode=TX_Only_Simplex_Unidirect_Master
PA7.Signal=SPI1_MOSI
PA8.GPIOParameters=GPIO_Label
PA8.GPIO_Label=GPIO_KEYPAD_COLUMN_3
PA8.Signal=GPIO_Input
PA9.GPIOParameters=GPIO_Label
PA9.GPIO_Label=GPIO_KEYPAD_COLUMN_2
PA9.Signal=GPIO_Input
PB12.Signal=GPIO_Output
PB13.Mode=TX_Only_Simplex_Unidirect_Master
PB13.Signal=SPI2_SCK
PB14.GPIOParameters=GPIO_Label
PB14.GPIO_Label=GPIO_KEYPAD_COLUMN_4
PB14.Signal=GPIO_Input
PB15.Mode=TX_Only_Simplex_Unidirect_Master
PB15.Signal=SPI2_MOSI
PB3.GPIOParameters=GPIO_Speed,GPIO_Label
PB3.GPIO_Label=GPIO_KEYPAD_ROW_3
PB3.GPIO_Speed=GPIO_SPEED_FREQ_HIGH
PB3.Signal=GPIO_Output
PB4.GPIOParameters=GPIO_Speed,GPIO_Label
PB4.GPIO_Label=GPIO_KEYPAD_ROW_2
PB4.GPIO_Speed=GPIO_SPEED_FREQ_HIGH
PB4.Signal=GPIO_Output
PB5.GPIOParameters=GPIO_Speed,GPIO_Label
PB5.GPIO_Label=GPIO_KEYPAD_ROW_1
PB5.GPIO_Speed=GPIO_SPEED_FREQ_HIGH
PB5.Signal=GPIO_Output
PB6.Mode=I2C
PB6.Signal=I2C1_SCL
PB7.Mode=I2C
PB7.Signal=I2C1_SDA
PC13-TAMPER-RTC.GPIOParameters=GPIO_Label
PC13-TAMPER-RTC.GPIO_Label=GPIO_USER_LED
PC13-TAMPER-RTC.Signal=GPIO_Output
PD0-OSC_IN.Mode=HSE-External-Oscillator
PD0-OSC_IN.Signal=RCC_OSC_IN
PD1-OSC_OUT.Mode=HSE-External-Oscillator
PD1-OSC_OUT.Signal=RCC_OSC_OUT
RCC.SYSCLKFreq_VALUE=72000000
RCC.SYSCLKSource=RCC_SYSCLKSOURCE_PLLCLK
board=custom

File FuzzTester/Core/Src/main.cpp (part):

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       2.4, 2.3       CD4052 2ch 4:1    Transistor 35~31
       2.7, 2.6, 2.5  CD4051 1ch 8:1    Transistor 15~ 8
   STM32:
     Keypad   : PB5 , PB4 , PB3 , PA15   Row 1-4, output
                PA12, PA11, PA10, PA9    Column 1-4, input, pull down resistor, debounce
     LCD      : PB7 , PB6                 I2C1
     74HC595's: PA5                      SPI1 SCK, Master Transmit Only, prescaler /4, to 74HC595N: 11: SRCLK
                PA7                      SPI1 MOSI                                     to 74HC595N: 14: SER
                PA6                      GPIO_Latch (RCLK)                             to 74HC595N: 12: RCLK
*/

/* USER CODE END Header */
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  GPIO_InitStruct.Speed = GPIO_SPEED_FREQ_LOW;
  HAL_GPIO_Init(GPIOA, &GPIO_InitStruct);

  /*Configure GPIO pin : PB11 */
  GPIO_InitStruct.Pin = GPIO_PIN_11;
  GPIO_InitStruct.Mode = GPIO_MODE_IT_RISING;
  GPIO_InitStruct.Pull = GPIO_NOPULL;
  HAL_GPIO_Init(GPIOB, &GPIO_InitStruct);

  /*Configure GPIO pins : PB12 GPIO_KEYPAD_ROW_3_Pin GPIO_KEYPAD_ROW_2_Pin GPIO_KEYPAD_ROW_1_Pin */
  GPIO_InitStruct.Pin = GPIO_PIN_12|GPIO_KEYPAD_ROW_3_Pin|GPIO_KEYPAD_ROW_2_Pin|GPIO_KEYPAD_ROW_1_Pin;
  GPIO_InitStruct.Mode = GPIO_MODE_OUTPUT_PP;
  GPIO_InitStruct.Pull = GPIO_NOPULL;
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
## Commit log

2020-01-30 1602 finished
2020-01-30 Test
2020-01-30 test6
2020-02-01 ToggleSwitch added
2020-02-08 Put classes in Component, created MyMain
2020-02-09 With subscribers
2020-02-09 Fixed HAL_Delay, used LCD
2020-02-09 CounterSwitch
2020-02-09 Base class for switches
2020-02-09 Renamed Switch to Button
2020-02-09 Action during pressing instead of releasing
2020-02-09 Moved functionality to Button base class
2020-02-09 Added momentary button
2020-02-09 Renamed Button to DefaultButton
2020-02-09 Predelay for hold, button
2020-02-09 Fixed bug when button while button debouncing.
2020-02-10 LCD Int is not working; removed from normal LCD delay, and refresh time by SysTick.
2020-02-16 states for buttons, long press works too.
2020-02-18 Keypad works, but without debouncing and hold
2020-02-22 Keypad only working for polling, used strong resistors (1K) instead of internal 50K pullup resistors. Used single state transition diagram.
2020-02-23 miche->Michel Keijzers
2020-02-23 Used GPIO definitions, improved KeyPad.
2020-02-23 Removed unused callback function from MomentaryButton.
2020-02-23 Fuzz Tester project (split off from Library Tester)
2020-02-25 Used HAL for keypad again (problems with own GPIO library).
2020-02-25 Due to new monitor, max line width = 100
2020-02-28 Improve LCD initialization
2020-02-29 Comments, UpdateLCD->Update, LCD Delay 5 in init, IOC
2020-02-29 Minor
2020-02-29 Changed version according jepael again.
2020-03-04 Fixed shift register values for leds.
2020-04-06 Added KiCad
2020-04-06 PCB fixes
2020-04-06 Changed power supply
2020-04-06 Improved PCB SPI/I2C lines
2020-04-06 Fixed unconnected PCB traces
2020-04-07 Schematics UI/MCU -> MCU + PCB improvements
2020-04-08 Power regulator -9V
2020-04-10 PCB Placement 100x82
2020-04-11 Starting to route
2020-04-12 More traces
2020-04-12 Transistors C almost done
2020-04-12 Routing finished, todo: AGND
2020-04-13 GNDA, PCB DRC fixed
2020-04-13 DRC OK
2020-04-13 Removed DRC errors, added logos
2020-04-15 MicroCap
2020-04-15 git ignore
2020-04-18 Analysis microcap
2020-04-20 New Kicad project (16 mux)
2020-04-20 Removed shift registers
2020-04-21 Finished (but not beautiful) PCB without SPI and most 8 channel multiplexers.
2020-04-22 EEProm code downloaded
2020-04-24 New structure
2020-04-24 Test
    Test
2020-04-25 LCD backlight and backlight removed from circuit/pcb.
2020-04-25 PCB Logo/texts
2020-04-26 EEprom + PCB changes
2020-04-26 logo, capacitors
    Logo, removed capacitors location, added fuz capcitors to back. TODO: change capacitors bank A.
2020-04-26 PCB and code
    Some PCB changes.
    HalUtils, multiplexer code, component code.
2020-05-05 PCB mostly
2020-05-06 Code + resistors
    Many code changes (UI) + resistors -> pulldowns.
2020-05-07 Fixed store problem
2020-05-07 Split MyMain
2020-05-08 Changed name (Michel Keijzers), relayout
2020-05-08 Freecad
2020-05-08 Converted Eeprom to a class
2020-05-09 Assert and const
2020-05-10 Wear leveling
2020-05-10 Migrated ioc
    Changed CPU speed to 4 MHz (minimum for LCD display)
2020-05-10 Fixed max virtual addresses for eeprom
2020-05-10 25K->16K Fuzz
2020-05-11 Owner's Manual
2020-05-19 Improvements according video youtube
2020-05-21 UART, BOOT, NRST, Isolated OSC gnd
2020-05-21 Thicker I2C trace
2020-05-27 Various
    Various
2020-05-28 STM32 DevBoard in Freecad
2020-05-28 Kicad 3_STM32DevBoard
2020-05-29 STM32 Dev Board
2020-05-29 Freecad positioning
2020-05-29 GitIgnore
2020-05-30 Remove 3V3 voltage regulation (get from STM32 5V)
